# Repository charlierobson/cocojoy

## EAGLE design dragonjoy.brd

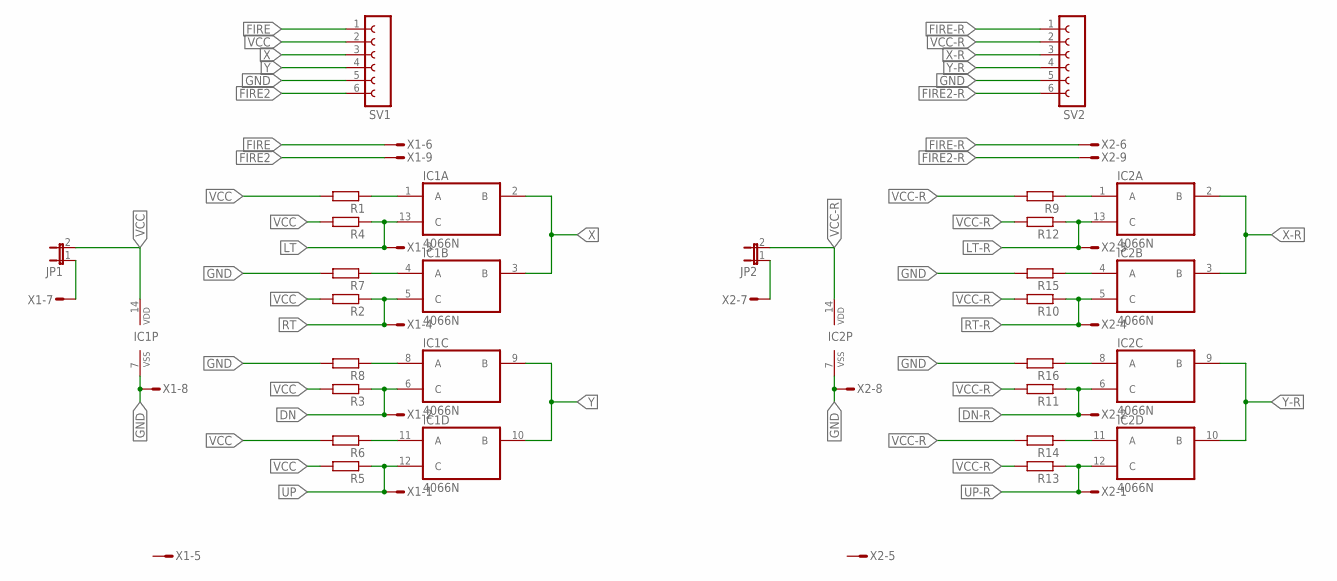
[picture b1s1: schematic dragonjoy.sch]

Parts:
IC1, IC2: 4066N; DIL14
JP1, JP2: JP1E; JP1
R1, R2, R3, R4, R5, R6, R7, R8, R9, R10, R11, R12, R13, R14, R15, R16: R-EU_0207/10; 0207/10
SV1, SV2: FE06-1; FE06
X1, X2: M09-182S; 182-009-MALE

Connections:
DN: IC1.6 (C), R3.1, X1.2
DN-R: IC2.6 (C), R11.1, X2.2
FIRE: SV1.1, X1.6
FIRE2: SV1.6, X1.9
FIRE2-R: SV2.6, X2.9
FIRE-R: SV2.1, X2.6
GND: IC1.7 (VSS), IC2.7 (VSS), R7.2, R8.2, R15.2, R16.2, SV1.5, SV2.5, X1.8, X2.8
LT: IC1.13 (C), R4.1, X1.3
LT-R: IC2.13 (C), R12.1, X2.3
unnamed: JP1.1, X1.7
unnamed: IC2.1 (A), R9.1
unnamed: IC1.1 (A), R1.1
unnamed: IC2.11 (A), R14.1
unnamed: IC2.4 (A), R15.1
unnamed: IC2.8 (A), R16.1
unnamed: JP2.1, X2.7
unnamed: IC1.11 (A), R6.1
unnamed: IC1.4 (A), R7.1
unnamed: IC1.8 (A), R8.1
RT: IC1.5 (C), R2.1, X1.4
RT-R: IC2.5 (C), R10.1, X2.4
UP: IC1.12 (C), R5.1, X1.1
UP-R: IC2.12 (C), R13.1, X2.1
VCC: IC1.14 (VDD), JP1.2, R1.2, R2.2, R3.2, R4.2, R5.2, R6.2, SV1.2
VCC-R: IC2.14 (VDD), JP2.2, R9.2, R10.2, R11.2, R12.2, R13.2, R14.2, SV2.2
X: IC1.2 (B), IC1.3 (B), SV1.3
X-R: IC2.2 (B), IC2.3 (B), SV2.3
Y: IC1.9 (B), IC1.10 (B), SV1.4
Y-R: IC2.9 (B), IC2.10 (B), SV2.4

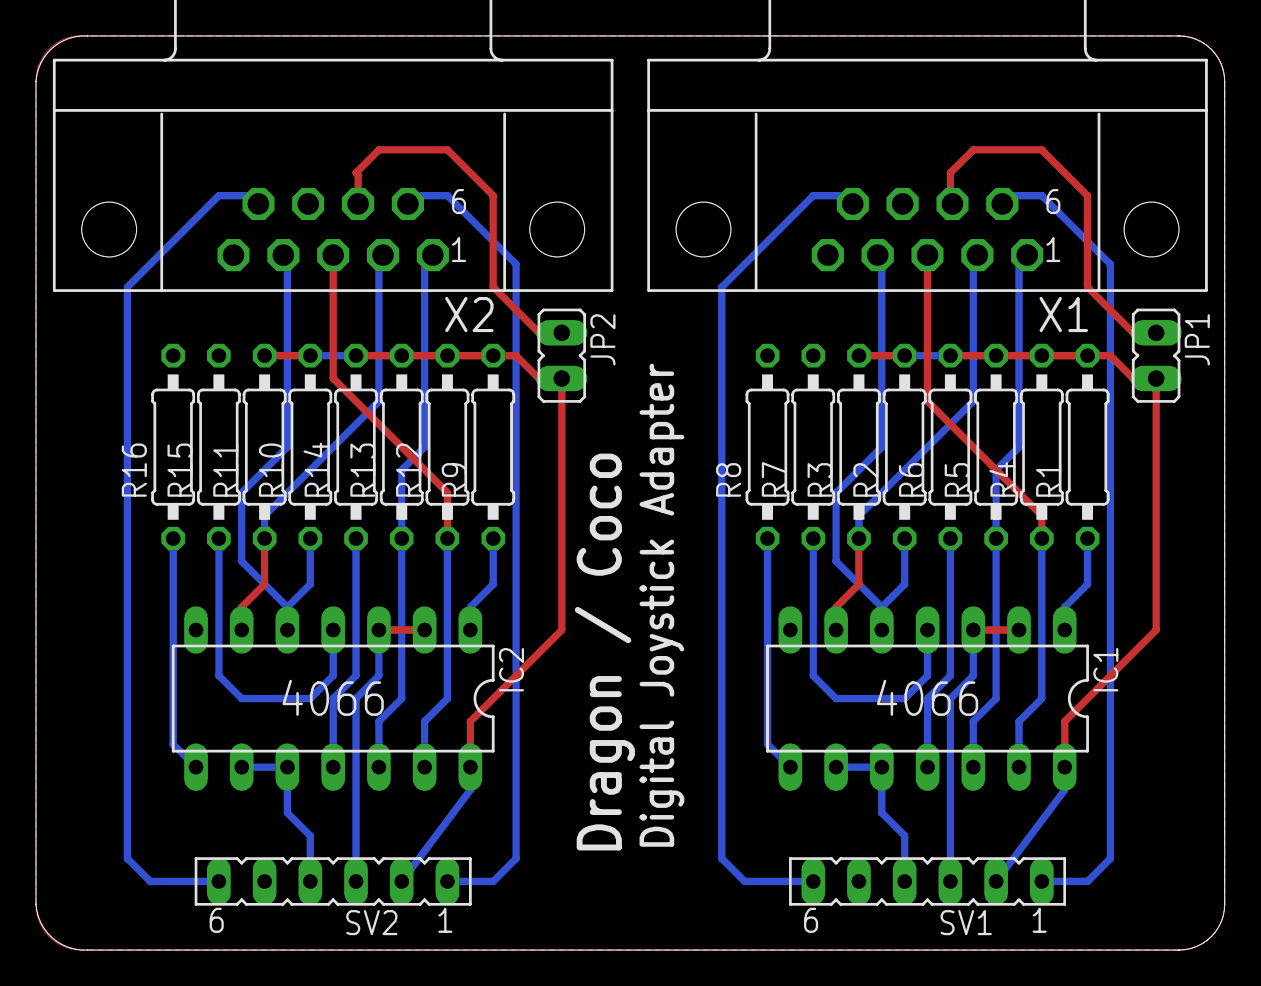
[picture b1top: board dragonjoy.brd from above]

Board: 2 copper layers, 66.0 x 50.8 mm, 24 parts (0 on the bottom side), 29 nets.

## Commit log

2016-09-23 add 90 degree connector
2016-09-23 update double board for printing and etching
2016-09-25 double up board elements at schematic level
2016-09-26 added original board back for debugging
2016-09-27 prepare for submission
2016-09-27 add production zip, tweak gerber job to add outline, remove mill
